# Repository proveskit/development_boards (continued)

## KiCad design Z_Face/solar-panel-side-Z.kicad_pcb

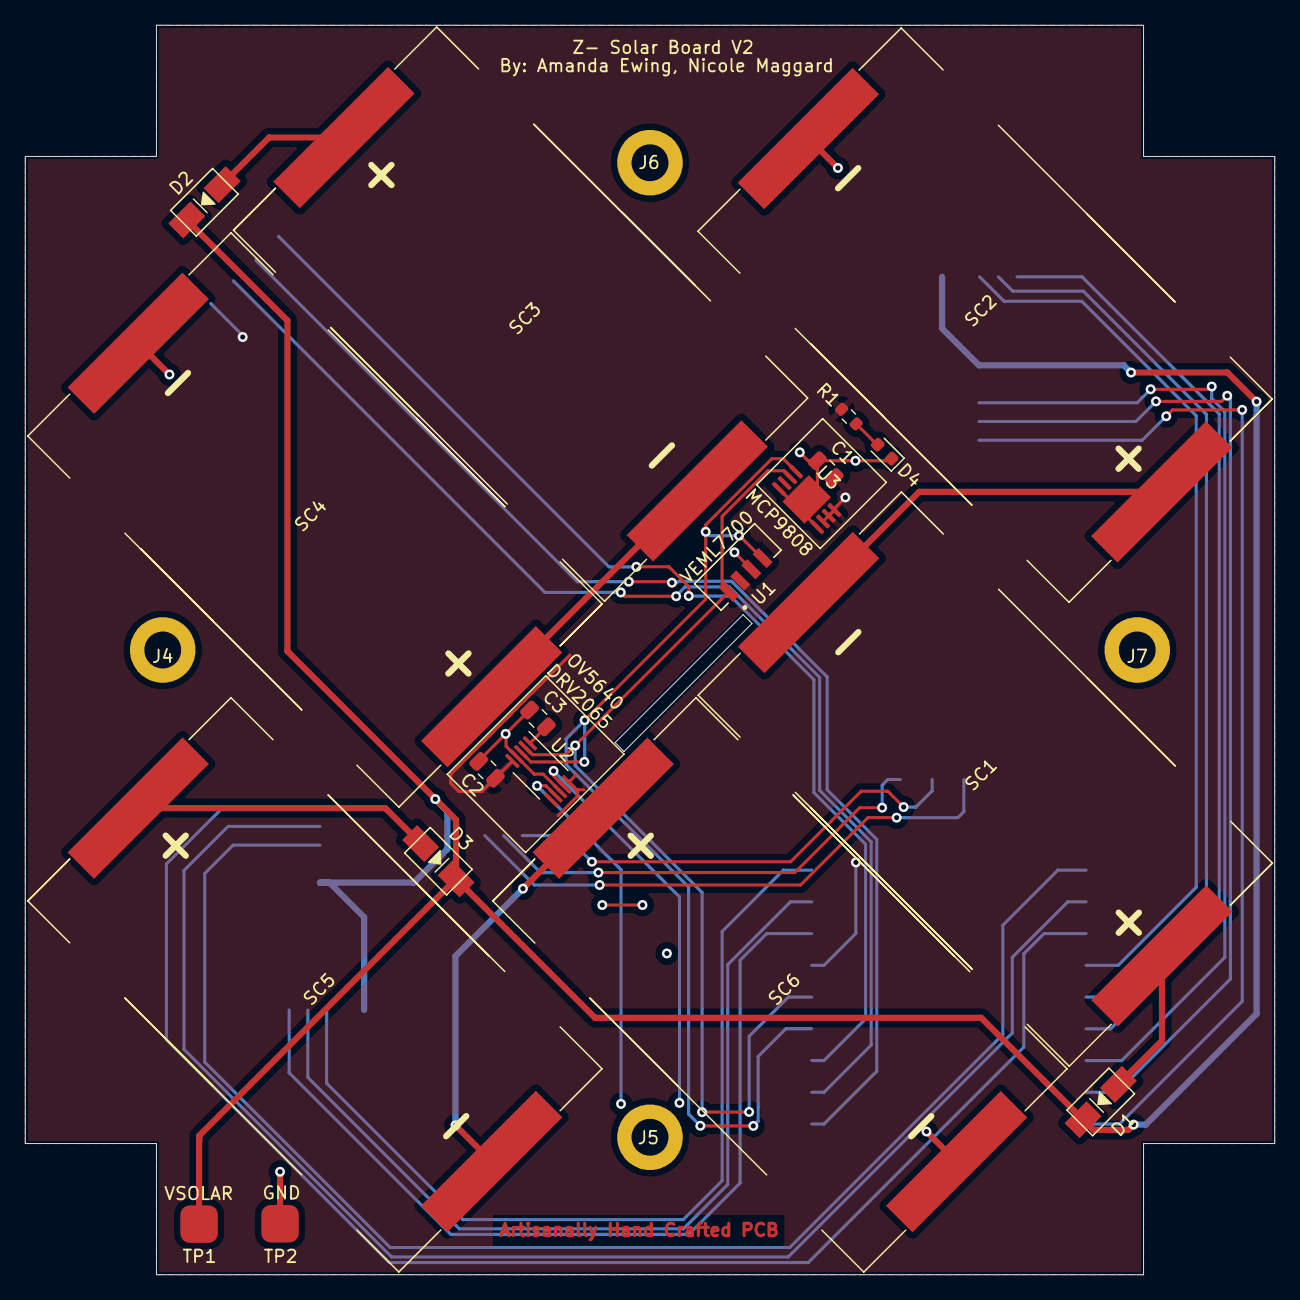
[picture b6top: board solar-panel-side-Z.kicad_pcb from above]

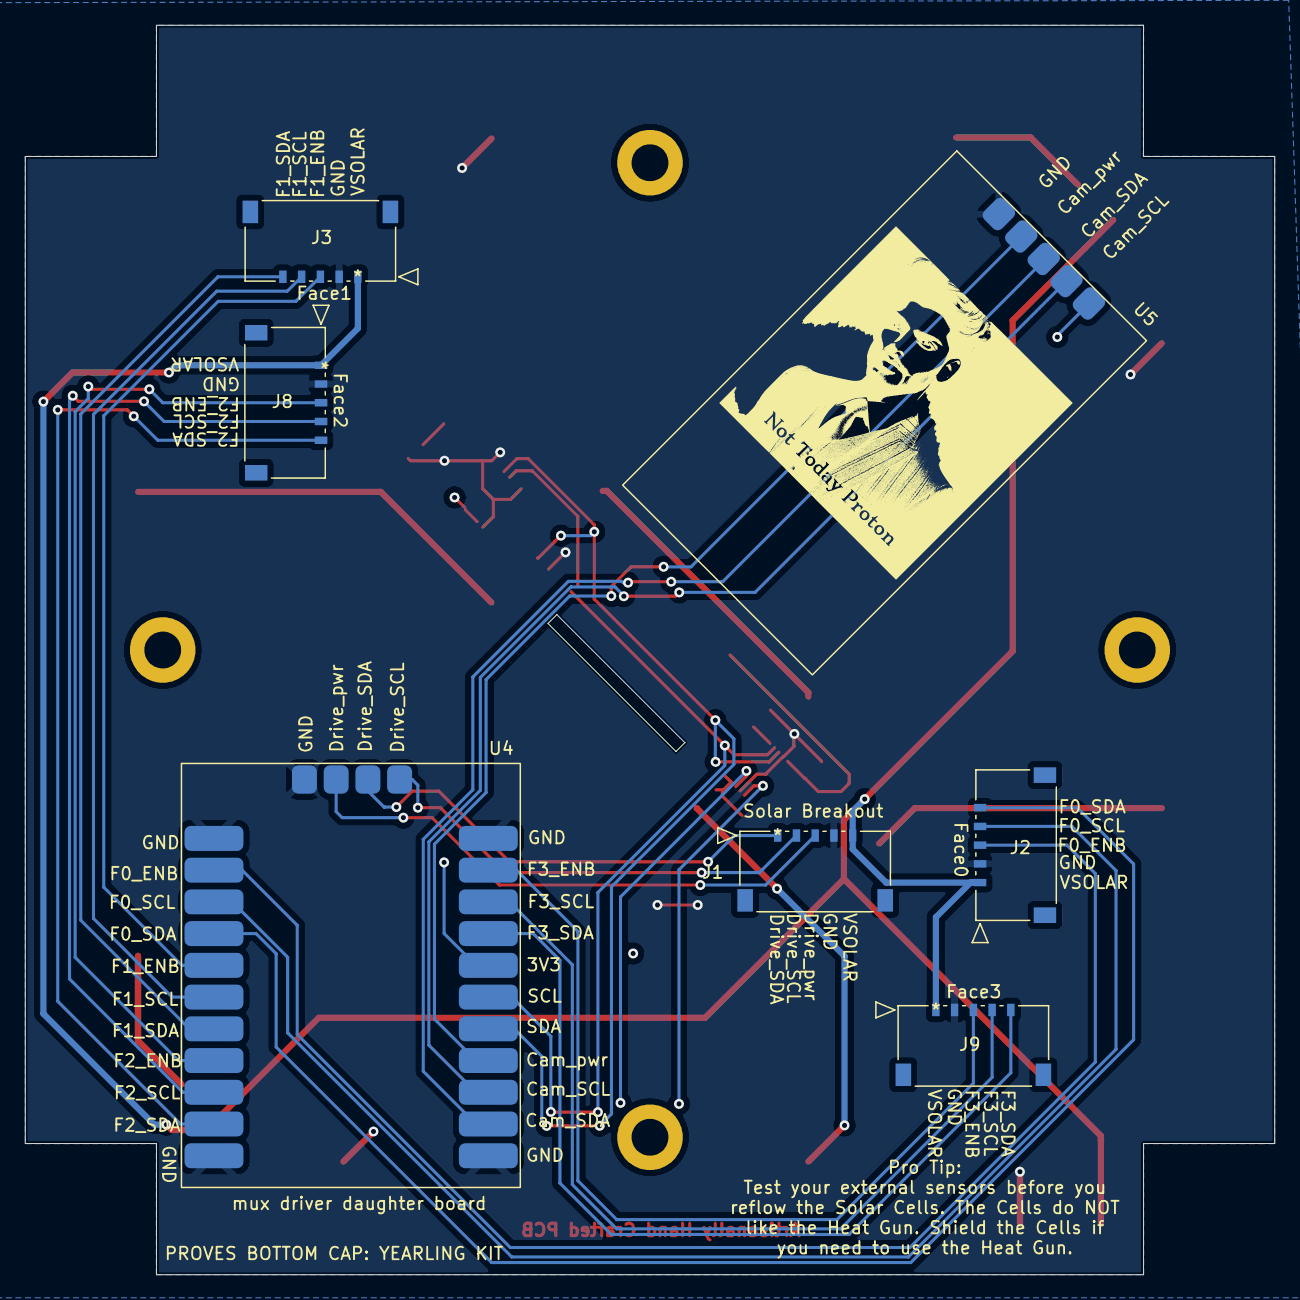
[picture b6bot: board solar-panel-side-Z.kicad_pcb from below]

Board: 4 copper layers, 100.0 x 100.0 mm, 30 parts (7 on the bottom side), 32 nets.

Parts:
C1, C2, C3: 1uF; C_0805_2012Metric
D1, D2, D3: CDBA240LL-HF; DO-214AC
D4: CQY99; LED_0603_1608Metric
J1: CON-5040500591; CON_5040500591
J2: Face0; CON_5040500591
J3: Face1; CON_5040500591
J4, J5, J6, J7: Conn_01x01; MountingHoles
J8: Face2; CON_5040500591
J9: Face3; CON_5040500591
R1: 1k; R_0603_1608Metric
SC1, SC2, SC3, SC4, SC5, SC6: SM101K07TF; KXOB101K08F-TR
TP1, TP2: TestPoint; Test Pad
U1: VEML7700; XDCR_VEML7700-TT
U2: DRV2605LDGS; VSSOP-10_3x3mm_P0.5mm
U3: MCP9808_DFN; MSOP-8-1EP_3x3mm_P0.65mm_EP2.5x3mm_Mask1.73x2.36mm
U4: mux_driver
U5: camera_daughter

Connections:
3v3_break: J1.3, U4.24 (3V3)
+3V3: C1.1, C2.1, R1.1, U1.2 (VDD), U2.5 (EN), U2.10 (VDD), U3.6 (A1), U3.7 (A0), U3.8 (VDD), U4.16 (F4PWR), U5.5 (3V3)
Camera_Pwr: U4.19 (XPWR), U5.2 (ctrl)
Camera_SCL: U4.20 (XSCL), U5.4 (SCL)
Camera_SDA: U4.21 (XSDA), U5.3 (SDA)
F0_ENB: J2.3, U4.2 (F0PWR)
F0_SCL: J2.4, U4.3 (F0SCL)
F0_SDA: J2.5, U4.4 (F0SDA)
F1_ENB: J3.3, U4.5 (F1PWR)
F1_SCL: J3.4, U4.6 (F1SCL)
F1_SDA: J3.5, U4.7 (F1SDA)
F2_ENB: J8.3, U4.8 (F2PWR)
F2_SCL: J8.4, U4.9 (F2SCL)
F2_SDA: J8.5, U4.10 (F2SDA)
F3_ENB: J9.3, U4.13 (F3PWR)
F3_SCL: J9.4, U4.14 (F3SCL)
F3_SDA: J9.5, U4.15 (F3SDA)
GND: C1.2, C2.2, C3.2, D4.1 (K), J1.4, J2.2, J3.2, J8.2, J9.2, SC2.2 (-), SC4.2 (-), SC6.2 (-), TP2.1, U1.3 (GND), U2.4 (IN/TRIG), U2.8 (GND), U3.4 (GND), U3.5 (A2), U3.9 (EP/GND), U4.1 (GND), U4.11 (GND), U4.12 (GND), U4.22 (GND), U4.23 (GND), U5.1 (GND)
unnamed: D1.2 (A), SC1.1 (+)
unnamed: D2.2 (A), SC3.1 (+)
unnamed: D3.2 (A), SC5.1 (+)
unnamed: D4.2 (A), R1.2
unnamed: SC1.2 (-), SC2.1 (+)
unnamed: SC3.2 (-), SC4.1 (+)
unnamed: SC5.2 (-), SC6.1 (+)
unnamed: U2.7 (OUT+), U2.9 (OUT-)
unnamed: C3.1, U2.1 (REG)
SCL: U1.1 (SCL), U2.2 (SCL), U3.2 (SCL), U4.17 (F4SCL)
SCL_Break: J1.2, U4.26 (SCL)
SDA: U1.4 (SDA), U2.3 (SDA), U3.1 (SDA), U4.18 (F4SDA)
SDA_Break: J1.1, U4.25 (SDA)
VSOLAR: D1.1 (K), D2.1 (K), D3.1 (K), J1.5, J2.1, J3.1, J8.1, J9.1, TP1.1

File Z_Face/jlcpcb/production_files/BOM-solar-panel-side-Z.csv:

Comment,Designator,Footprint,LCSC
MCP9808_DFN,U3,MSOP-8-1EP_3x3mm_P0.65mm_EP2.5x3mm_Mask1.73x2.36mm,C129490
VEML7700,U1,XDCR_VEML7700-TT,C1850416
1k,R1,R_0603_1608Metric,C21190
CQY99,D4,LED_0603_1608Metric,C2288
1uF,"C1,C2,C3",C_0805_2012Metric,C28323
CDBA240LL-HF,"D1,D2,D3",DO-214AC,C2886093
DRV2605LDGS,U2,VSSOP-10_3x3mm_P0.5mm,C527464
Conn_01x01,J4,MountingHoles,
Conn_01x01,J5,MountingHoles,
Conn_01x01,J6,MountingHoles,
Conn_01x01,J7,MountingHoles,
TestPoint,TP1,Test Pad,
SM101K07TF,SC5,KXOB101K08F-TR,
TestPoint,TP2,Test Pad,
SM101K07TF,SC3,KXOB101K08F-TR,
SM101K07TF,SC4,KXOB101K08F-TR,
SM101K07TF,SC6,KXOB101K08F-TR,
SM101K07TF,SC1,KXOB101K08F-TR,
CON-5040500591,J1,CON_5040500591,
~,U5,camera_daughter,
Face0,J2,CON_5040500591,
Face1,J3,CON_5040500591,
~,U4,mux_driver,
SM101K07TF,SC2,KXOB101K08F-TR,
Face3,J9,CON_5040500591,
Face2,J8,CON_5040500591,

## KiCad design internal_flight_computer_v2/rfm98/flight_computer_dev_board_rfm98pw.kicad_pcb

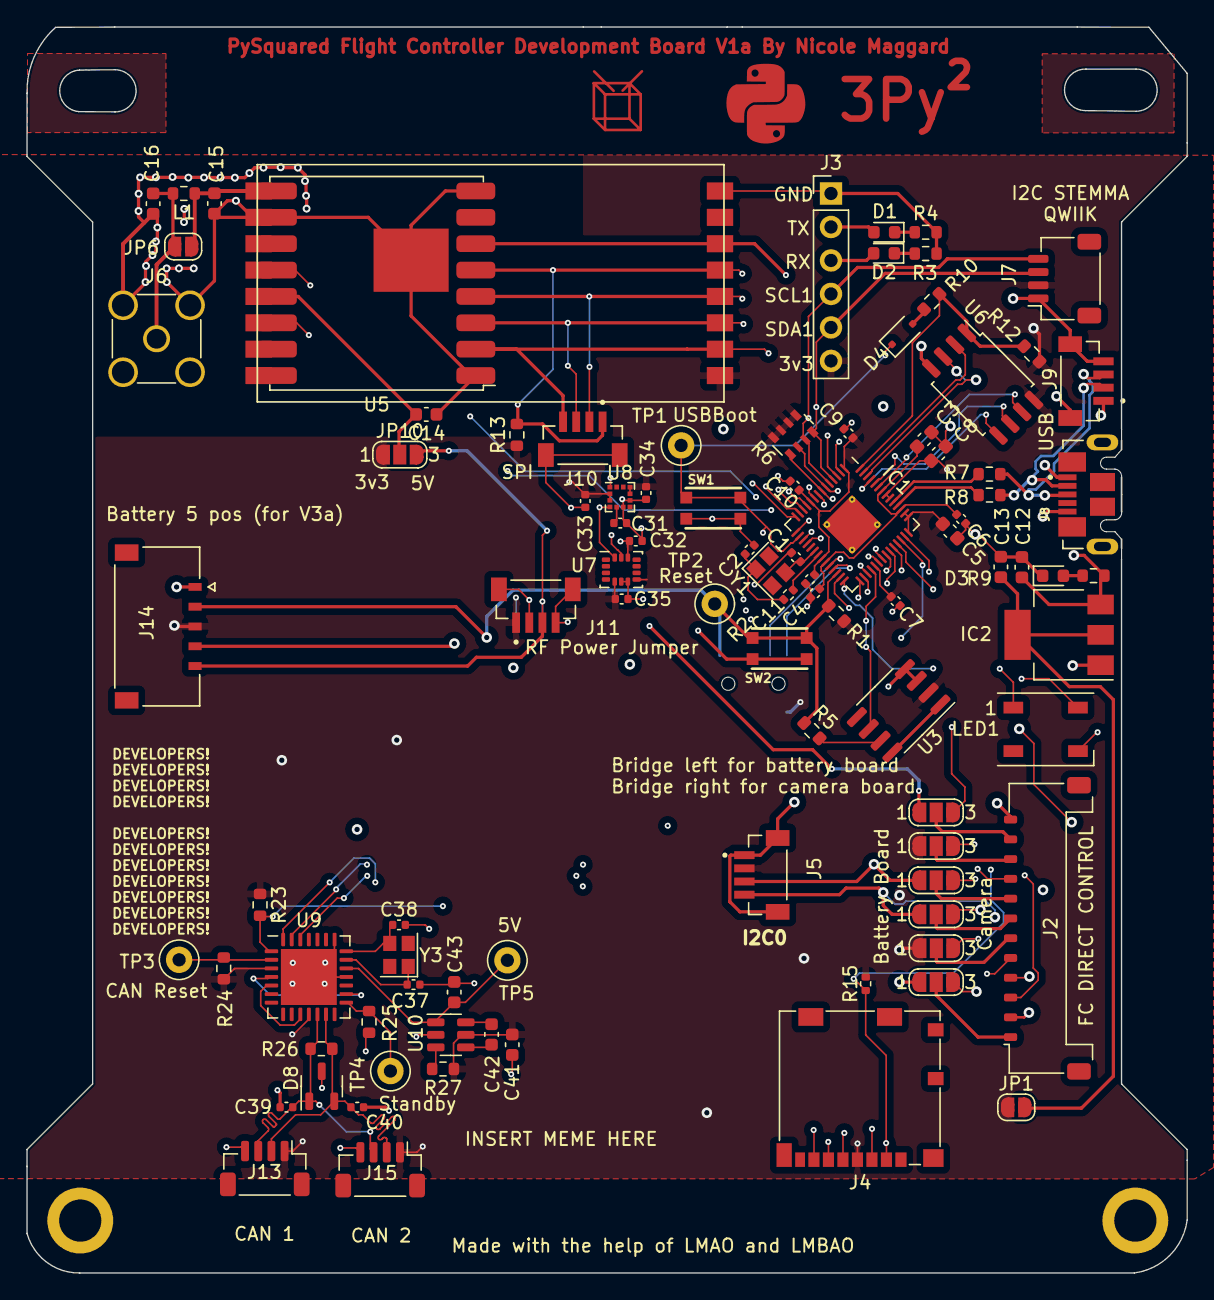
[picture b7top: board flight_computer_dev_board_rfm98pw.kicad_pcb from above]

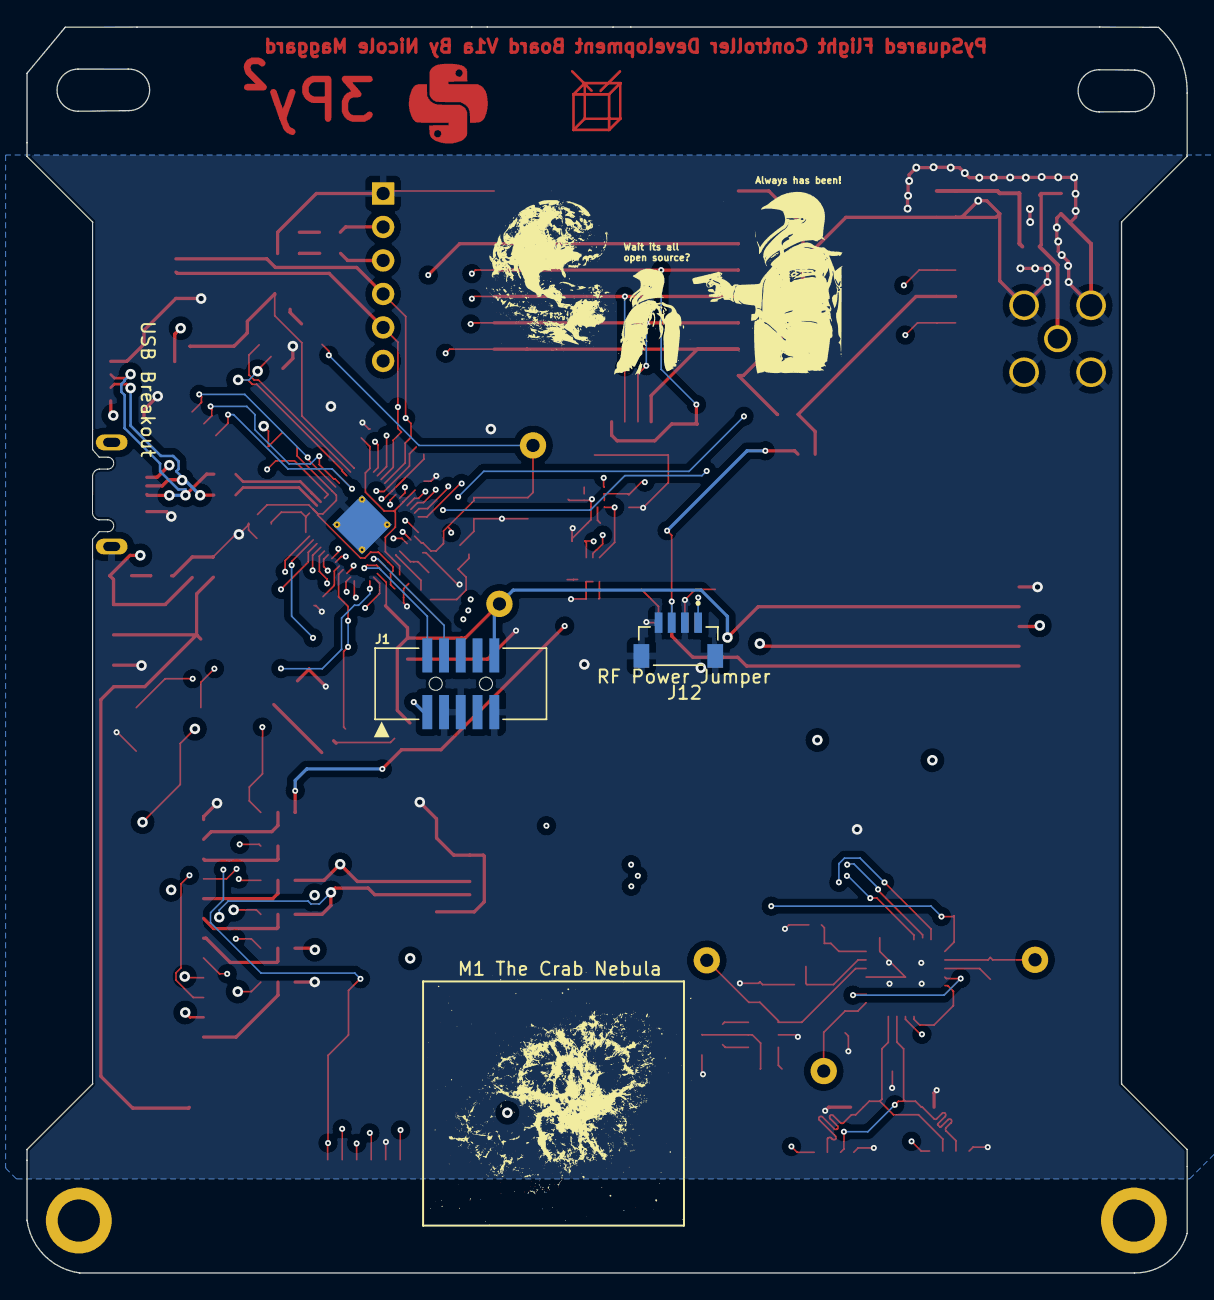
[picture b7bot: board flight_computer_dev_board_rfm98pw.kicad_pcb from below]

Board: 4 copper layers, 88.0 x 94.5 mm, 96 parts (2 on the bottom side), 80 nets.

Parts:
C1, C2: 22pF; C_0402_1005Metric
C3, C6, C8: 1uF; C_0603_1608Metric
C4, C5, C7, C9, C10, C11, C32, C33, C34, C35: 100nf; C_0402_1005Metric
C12, C14: 10uF; C_0603_1608Metric
C13: 22uF; C_0603_1608Metric
C15, C16: DNI; C_0603_1608Metric
C31: 220nf; C_0402_1005Metric
C37, C38: 22pf; C_0402_1005Metric
C39, C40: 47pf; C_0402_1005Metric
C41, C43: 10uf; C_0603_1608Metric
C42: 1uf; C_0603_1608Metric
D1, D2, D3: LED; LED_0603_1608Metric
D4: NSR0320; D_SOD-323F
D8: PESD1CAN; SOT-23-3
IC1: RP2040_QFN56; QFN-56-1EP_7x7mm_P0.4mm_EP3.2x3.2mm_ThermalVias
IC2: AZ1117CH-3.3TRG1; SOT-223
J1: Conn_ARM_JTAG_SWD_10; JTAG_2X05_1.27MM_BOX_NOCREAM
J2: FC to EPS Connector; Molex_Pico-Lock_504050-1291_1x12-1MP_P1.50mm_Horizontal
J3: Life Makes Lemonade; PinHeader_1x06_P2.54mm_Vertical
J4: 104031-0811; microSD_HC_Molex_104031-0811
J5, J9, J10, J11, J12: BM04B-SRSS-TB(LF)(SN); JST_BM04B-SRSS-TB(LF)(SN)
J6: Conn_Coaxial; SMA_Amphenol_901-144_Vertical
J7: Breakout; JST_SH_SM04B-SRSS-TB_1x04-1MP_P1.00mm_Horizontal
J8: USB_B_Micro; MOLEX_105164-0001
J13, J15: Breakout; JST_SH_BM04B-SRSS-TB_1x04-1MP_P1.00mm_Vertical
J14: Battery; MOLEX_5040500591
JP1, JP6: SolderJumper_2_Open; SolderJumper-2_P1.3mm_Open_RoundedPad1.0x1.5mm
JP3, JP4, JP5, JP7, JP8, JP9, JP10: Jumper_3_Open; SolderJumper-3_P1.3mm_Open_RoundedPad1.0x1.5mm_NumberLabels
L1: DNI; R_0603_1608Metric
LED1: WS2812B_SK6812_1515; LED_WS2812B_PLCC4_5.0x5.0mm_P3.2mm
R1, R5, R9, R12, R13, R23, R24, R25, R27: 10k; R_0603_1608Metric
R2: 1k; R_0402_1005Metric
R3, R4, R10: 1k; R_0603_1608Metric
R6: 10k; R_Array_Convex_4x0603
R7, R8: 22; R_0603_1608Metric
R15: 10k; R_0402_1005Metric
R26: 120; R_0603_1608Metric
SW1, SW2: KMR2; BTN_KMR2_4.6X2.8
TP1: USBBOOT; TestPoint_Loop_D1.80mm_Drill1.0mm_Beaded
TP2, TP3: RESET; TestPoint_Loop_D1.80mm_Drill1.0mm_Beaded
TP4: Standby; TestPoint_Loop_D1.80mm_Drill1.0mm_Beaded
TP5: 5V; TestPoint_Loop_D1.80mm_Drill1.0mm_Beaded
U3: MAX706RESA; SO-8_3.9x4.9mm_P1.27mm
U4: RFM98PW
U5: RFM9xBreakout; HOPERF_RFM9XW_SMD
U6: W25Q128JV; SOIC-8_5.275x5.275mm_P1.27mm
U7: LSM6DSOTR; LGA-14_3x2.5mm_P0.5mm_LayoutBorder3x4y
U8: LSM303AGRTR; LGA-12_2x2mm_P0.5mm
U9: MCP25625-E/ML; QFN-28-1EP_6x6mm_P0.65mm_EP4.25x4.25mm
U10: AP3602AKTR-G1; SOT-23-6
Y1: 12MHZ; Crystal_SMD_2520-4Pin_2.5x2.0mm
Y3: 16MHZ 12 pf; Crystal_SMD_2520-4Pin_2.5x2.0mm

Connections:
1.2V: C3.1, C4.2, C5.2, IC1.23 (DVDD), IC1.45 (VREG_VOUT), IC1.50 (DVDD)
3.3V: C6.1, C7.1, C8.1, C9.1, C10.1, C11.1, C32.1, C33.1, C34.1, C35.1, C41.2, IC1.1 (IOVDD), IC1.10 (IOVDD), IC1.22 (IOVDD), IC1.33 (IOVDD), IC1.42 (IOVDD), IC1.43 (ADC_IOVDD), IC1.44 (VREG_IOVDD), IC1.48 (USB_IOVDD), IC1.49 (IOVDD), J1.1 (VTref), J3.6, J4.4 (VDD), J5.2, J7.2, J11.1, J12.1, J13.1, J14.3, J15.1, JP1.1 (A), JP4.1 (A), JP5.1 (A), JP10.1 (A), R1.1, R6.5 (R4.2), R6.6 (R3.2), R6.7 (R2.2), R6.8 (R1.2), R12.1, R13.1, R15.2, R23.1, R24.1, R27.1, U3.2 (VCC), U4.9 (3.3V), U6.8 (VCC), U7.5 (VDDIO), U7.8 (VDD), U7.12 (CS), U8.2 (CS_XL), U8.3 (CS_MAG), U8.9 (VDD), U8.10 (VDD_IO), U9.3 (VDD@1), U9.11 (VIO), U10.5 (VIN)
3v3 Spec: C13.1, IC2.2 (OUTPUT), IC2.4 (VOUT), JP1.2 (B)
+5V: C43.2, TP5.1, U9.19 (VDDA), U10.1 (VOUT)
/D+: IC1.47 (USB_D+), R7.1
/D-: IC1.46 (USB_D-), R8.1
/QSPI_CS: IC1.56 (~QSPI_CS), R10.1, R12.2, U6.1 (SSEL)
/QSPI_DATA[0]: IC1.53 (QSPI_SD0), U6.5 (MOSI)
/QSPI_DATA[1]: IC1.55 (QSPI_SD1), U6.2 (MISO)
/QSPI_DATA[2]: IC1.54 (QSPI_SD2), U6.3 (WP#/IO2)
/QSPI_DATA[3]: IC1.51 (QSPI_SD3), U6.7 (HOLD#/IO3)
/QSPI_SCK: IC1.52 (QSPI_SCLK), U6.6 (SCK)
BURN_RELAY_A / D5: IC1.18 (GPIO15), JP9.3 (B)
CANH: C40.2, D8.2, J13.2, J15.2, R26.2, U9.13 (CANH)
CANL: C39.1, D8.1, J13.3, J15.3, R26.1, U9.12 (CANL)
D0: IC1.41 (GPIO29/AD3), J14.4
D3: D4.1 (K), IC1.16 (GPIO13), J2.5, SW1.A, SW1.A' (P1), TP1.1
D6: IC1.27 (GPIO16), JP8.3 (B)
D7: IC1.28 (GPIO17), J2.9
D8: IC1.29 (GPIO18), JP5.3 (B)
D9: IC1.30 (GPIO19), JP7.3 (B)
ENABLE_BURN / PC: IC1.8 (GPIO6), J2.3
ENAB_RF / D2: IC1.15 (GPIO12), J2.4
FC_RESET: IC1.26 (/RUN), J1.10 (~RESET), J14.2, R1.2, R5.1, SW2.A, SW2.A' (P1), TP2.1
GND: C1.1, C2.1, C3.2, C4.1, C5.1, C6.2, C7.2, C8.2, C9.2, C10.2, C11.2, C12.2, C13.2, C14.1, C15.2, C16.2, C31.2, C32.2, C33.2, C34.2, C35.2, C37.2, C38.2, C39.2, C40.1, C41.1, C43.1, D3.1 (K), D8.3, IC1.57 (GND), IC2.1 (ADJ/GND), J1.3 (GND), J1.5 (GND), J1.9 (GNDDetect), J2.12, J3.1, J4.6 (VSS), J5.1, J5.S1 (SHIELD), J5.S2 (SHIELD), J6.2 (Ext), J7.1, J8.5 (GND), J8.SH1 (Shield), J9.4, J9.S1 (SHIELD), J9.S2 (SHIELD), J10.S1 (SHIELD), J10.S2 (SHIELD), J11.2, J11.4, J11.S1 (SHIELD), J11.S2 (SHIELD), J12.2, J12.4, J12.S1 (SHIELD), J12.S2 (SHIELD), J13.4, J14.1, J15.4, JP3.1 (A), LED1.3 (GND), R3.2, R4.2, R25.1, SW1.B (S), SW1.B' (S1), SW2.B (S), SW2.B' (S1), U3.3 (GND), U3.4 (PFI), U4.2 (GND), U4.16 (GND), U4.17 (GND), U5.1 (GND), U5.8 (GND), U5.10 (GND), U6.4 (VSS), U7.6 (GND), U7.7 (GND), U8.6 (GND), U8.8 (GND), U9.18 (VSS@1), U9.22 (GND), U9.29 (GND@1), U10.2 (GND)
HS: IC1.37 (GPIO25), JP3.3 (B)
I2C_RESET / VS: IC1.9 (GPIO7), J2.2
NEOPIX: IC1.36 (GPIO24), LED1.4 (DI)
Neo_pwr: IC1.39 (GPIO27/AD1), LED1.1 (VDD)
unnamed: C2.2, R2.2, Y1.1
unnamed: D1.1 (K), R4.1
unnamed: D2.1 (K), R3.1
unnamed: D3.2 (A), R9.2
unnamed: D4.2 (A), R10.2
unnamed: C1.2, IC1.20 (XIN), Y1.3 (2)
unnamed: IC1.21 (XOUT), R2.1
unnamed: J2.1, JP3.2 (C)
unnamed: J2.6, JP4.2 (C)
unnamed: J2.7, JP9.2 (C)
unnamed: J2.8, JP8.2 (C)
unnamed: J2.10, JP5.2 (C)
unnamed: J2.11, JP7.2 (C)
unnamed: C16.1, J6.1 (In), JP6.1 (A), L1.2
unnamed: U3.1 (~MR), U3.8 (~WDO)
unnamed: R5.2, U3.7 (~RESET)
unnamed: C31.1, U8.5 (C1)
unnamed: C38.1, U9.21 (OSC1), Y3.3 (2)
unnamed: C37.1, U9.20 (OSC2), Y3.1
unnamed: R24.2, TP3.1, U9.2 (RESET)
unnamed: R25.2, TP4.1, U9.15 (STBY)
unnamed: R27.2, U10.3 (*SHDN)
unnamed: C42.2, U10.6 (C+)
unnamed: C42.1, U10.4 (C-)
RF1_ANT: C15.1, JP6.2 (B), L1.1, U4.1 (ANT), U5.9 (ANT)
RF1_IO0: IC1.35 (GPIO23), U4.6 (GPIO_0), U5.14 (DIO0)
RF1_IO4: IC1.34 (GPIO22), U4.4 (GPIO_4), U5.12 (BUSY)
RF1_RST: IC1.31 (GPIO20), U4.14 (RESET), U5.6 (~RESET)
RF_VCC: C14.2, JP10.2 (C), U4.5 (VCC), U5.13 (3V3)
RX: D2.2 (A), IC1.3 (GPIO1), J3.3
RXCAN: U9.5 (RXCAN), U9.10 (RXD)
SCL0: IC1.7 (GPIO5), J5.4, JP9.1 (A), R6.1 (R1.1)
SCL1: IC1.5 (GPIO3), J3.4, J7.4, R6.3 (R3.1), U7.13 (SCL), U8.1 (SCL/SPC)
SDA0: IC1.6 (GPIO4), J5.3, JP8.1 (A), R6.2 (R2.1)
SDA1: IC1.4 (GPIO2), J3.5, J7.3, R6.4 (R4.1), U7.14 (SDA), U8.4 (SDA/SDI/SDO)
SPI0_CS0: IC1.12 (GPIO9), J10.1, R13.2, U4.13 (NSS), U5.5 (CS)
SPI0_CS1: IC1.38 (GPIO26/AD0), J4.2 (CD/DAT3), R15.1
SPI0_CS2: IC1.40 (GPIO28/AD2), R23.2, U9.1 (CS)
SPI0_MISO: IC1.11 (GPIO8), J4.7 (DAT0), J10.4, U4.10 (MISO), U5.2 (MISO), U9.28 (SO)
SPI0_MOSI: IC1.14 (GPIO11), J4.3 (CMD), J10.3, U4.11 (MOSI), U5.3 (MOSI), U9.27 (SI)
SPI0_SCK: IC1.13 (GPIO10), J4.5 (CLK), J10.2, U4.12 (SCK), U5.4 (SCK), U9.26 (SCK)
SWCLK: IC1.24 (SWCLK), J1.4 (SWDCLK/TCK)
SWDIO: IC1.25 (SWDIO), J1.2 (SWDIO/TMS)
TX: D1.2 (A), IC1.2 (GPIO0), J3.2
TXCAN: U9.4 (TXCAN), U9.16 (TXD)
USB_D+: J8.3 (D+), J9.3, R7.2
USB_D-: J8.2 (D-), J9.2, R8.2
VBUS: C12.1, IC2.3 (INPUT), J8.1 (VBUS), J9.1, R9.1
VBUS_RESET / D4: IC1.17 (GPIO14), JP4.3 (B)
VCC_RF1: J11.3, J12.3, J14.5, JP7.1 (A), JP10.3 (B)
WDT_WDI: IC1.32 (GPIO21), U3.6 (~WDI)

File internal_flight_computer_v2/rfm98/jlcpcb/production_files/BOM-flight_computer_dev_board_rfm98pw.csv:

Comment,Designator,Footprint,LCSC
10k,R6,R_Array_Convex_4x0603,C111802
1k,R2,R_0402_1005Metric,C11702
LED,"D1,D3",LED_0603_1608Metric,C12065
LSM303AGRTR,U8,LGA-12_2x2mm_P0.5mm,C126671
100nf,"C10,C11,C32,C33,C34,C35,C4,C5,C7,C9",C_0402_1005Metric,C1525
22pF,"C1,C2,C37,C38",C_0402_1005Metric,C1555
47pf,"C39,C40",C_0402_1005Metric,C1567
PESD1CAN,D8,SOT-23-3,C15771
1uF,"C3,C42,C6,C8",C_0603_1608Metric,C15849
BM04B-SRSS-TB(LF)(SN),"J10,J11,J12,J5,J9",JST_BM04B-SRSS-TB(LF)(SN),C160390
Breakout,"J13,J15,J7",JST_SH_SM04B-SRSS-TB_1x04-1MP_P1.00mm_Horizontal,C160404
220nf,C31,C_0402_1005Metric,C16772
MCP25625-E/ML,U9,QFN-28-1EP_6x6mm_P0.65mm_EP4.25x4.25mm,C191253
10uF,"C12,C14,C41,C43",C_0603_1608Metric,C19702
RP2040_QFN56,IC1,QFN-56-1EP_7x7mm_P0.4mm_EP3.2x3.2mm_ThermalVias,C2040
1k,"R10,R3,R4",R_0603_1608Metric,C21190
120,R26,R_0603_1608Metric,C22787
LED,D2,LED_0603_1608Metric,C2286
22,"R7,R8",R_0603_1608Metric,C23345
USB_B_Micro,J8,MOLEX_105164-0001,C234179
12MHZ,Y1,Crystal_SMD_2520-4Pin_2.5x2.0mm,C252259
10k,R15,R_0402_1005Metric,C25744
10k,"R1,R12,R13,R23,R24,R25,R27,R5,R9",R_0603_1608Metric,C25804
LSM6DSOTR,U7,LGA-14_3x2.5mm_P0.5mm_LayoutBorder3x4y,C2655100
MAX706RESA,U3,SO-8_3.9x4.9mm_P1.27mm,C28380
16MHZ 12 pf,Y3,Crystal_SMD_2520-4Pin_2.5x2.0mm,C284158
WS2812B_SK6812_1515,LED1,LED_WS2812B_PLCC4_5.0x5.0mm_P3.2mm,C2843785
AP3602AKTR-G1,U10,SOT-23-6,C460358
NSR0320,D4,D_SOD-323F,C48192
104031-0811,J4,microSD_HC_Molex_104031-0811,C585350
22uF,C13,C_0603_1608Metric,C59461
KMR2,"SW1,SW2",BTN_KMR2_4.6X2.8,C72443
AZ1117CH-3.3TRG1,IC2,SOT-223,C92102
W25Q128JV,U6,SOIC-8_5.275x5.275mm_P1.27mm,C97521
Conn_Coaxial,J6,SMA_Amphenol_901-144_Vertical,
DNI,C16,C_0603_1608Metric,
DNI,L1,R_0603_1608Metric,
SolderJumper_2_Open,JP1,SolderJumper-2_P1.3mm_Open_RoundedPad1.0x1.5mm,
DNI,C15,C_0603_1608Metric,
RFM98PW,U4,RFM98PW,
RESET,TP2,TestPoint_Loop_D1.80mm_Drill1.0mm_Beaded,
SolderJumper_2_Open,JP6,SolderJumper-2_P1.3mm_Open_RoundedPad1.0x1.5mm,
Jumper_3_Open,JP5,SolderJumper-3_P1.3mm_Open_RoundedPad1.0x1.5mm_NumberLabels,
RFM9xBreakout,U5,HOPERF_RFM9XW_SMD,
Jumper_3_Open,JP4,SolderJumper-3_P1.3mm_Open_RoundedPad1.0x1.5mm_NumberLabels,
FC to EPS Connector,J2,Molex_Pico-Lock_504050-1291_1x12-1MP_P1.50mm_Horizontal,
USBBOOT,TP1,TestPoint_Loop_D1.80mm_Drill1.0mm_Beaded,
Jumper_3_Open,JP3,SolderJumper-3_P1.3mm_Open_RoundedPad1.0x1.5mm_NumberLabels,
Life Makes Lemonade,J3,PinHeader_1x06_P2.54mm_Vertical,
Conn_ARM_JTAG_SWD_10,J1,JTAG_2X05_1.27MM_BOX_NOCREAM,
Jumper_3_Open,JP8,SolderJumper-3_P1.3mm_Open_RoundedPad1.0x1.5mm_NumberLabels,
Standby,TP4,TestPoint_Loop_D1.80mm_Drill1.0mm_Beaded,
RESET,TP3,TestPoint_Loop_D1.80mm_Drill1.0mm_Beaded,
Jumper_3_Open,JP7,SolderJumper-3_P1.3mm_Open_RoundedPad1.0x1.5mm_NumberLabels,
5V,TP5,TestPoint_Loop_D1.80mm_Drill1.0mm_Beaded,
Jumper_3_Open,JP9,SolderJumper-3_P1.3mm_Open_RoundedPad1.0x1.5mm_NumberLabels,
Battery,J14,MOLEX_5040500591,
Jumper_3_Open,JP10,SolderJumper-3_P1.3mm_Open_RoundedPad1.0x1.5mm_NumberLabels,

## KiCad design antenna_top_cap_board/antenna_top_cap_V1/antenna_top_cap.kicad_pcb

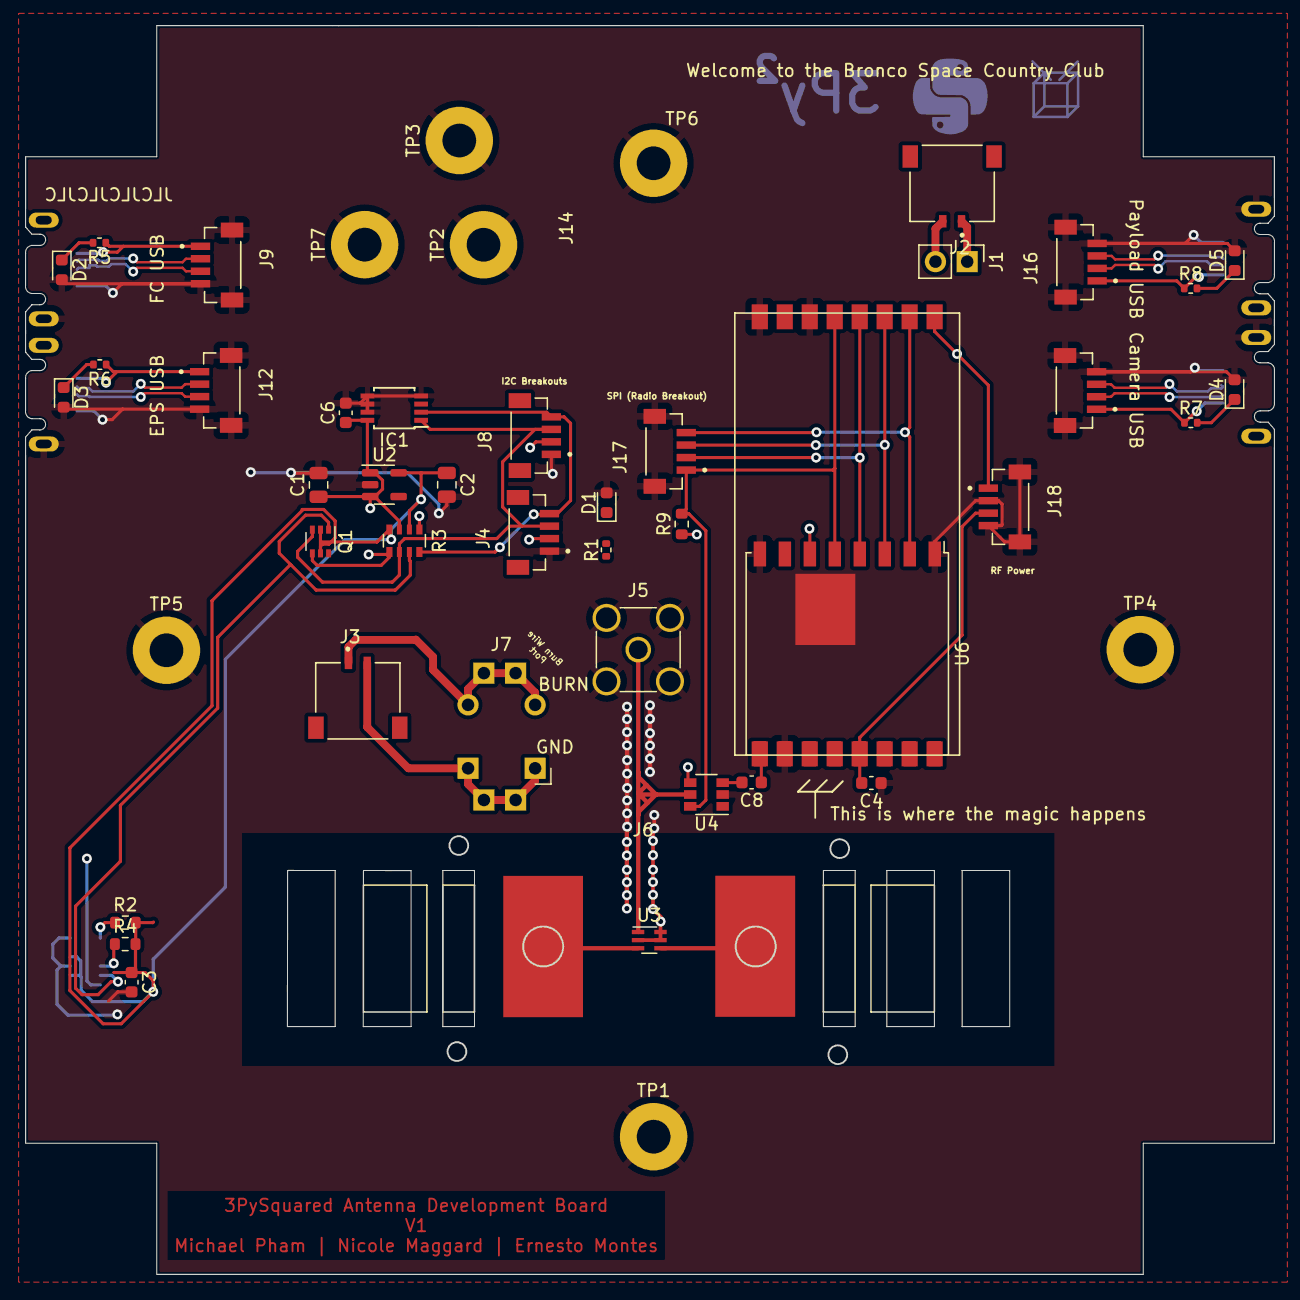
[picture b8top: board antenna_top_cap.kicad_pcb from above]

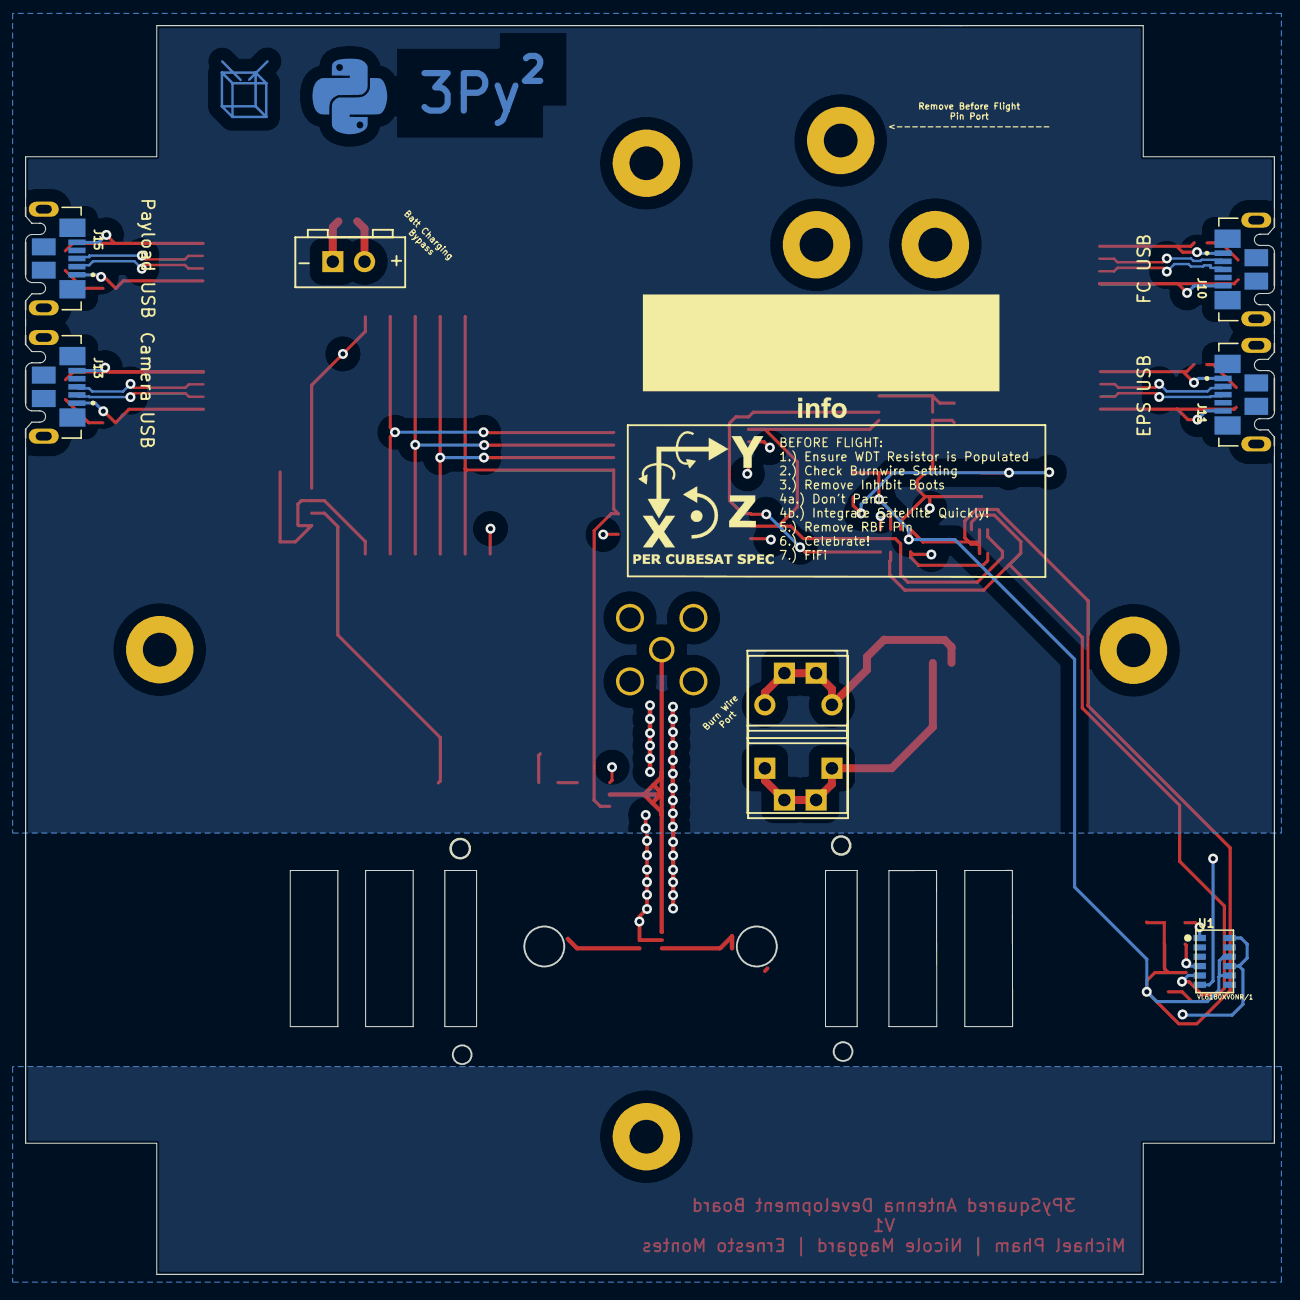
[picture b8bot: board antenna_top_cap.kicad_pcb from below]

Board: 4 copper layers, 100.0 x 100.0 mm, 53 parts (5 on the bottom side), 42 nets.

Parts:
C1, C2: 10uF; C_0805_2012Metric
C3: 0.1uF; C_0603_1608Metric
C4: 10uF; C_0603_1608Metric
C6: 100nf; C_0603_1608Metric
C8: 100pf; C_0603_1608Metric
D1, D2, D3, D4, D5: Blue; LED_0603_1608Metric
IC1: PCT2075DP,118; TSSOP-8_3x3mm_P0.65mm
J1: Battery Charge Bypass; PinHeader_1x02_P2.54mm_Vertical
J2: Battery Charge Bypass; MOLEX_504050-0291
J3: Burn_Wire; MOLEX_504050-0291
J4, J8, J9, J12, J14, J16, J17, J18: BM04B-SRSS-TB(LF)(SN); JST_BM04B-SRSS-TB(LF)(SN)
J5: Conn_Coaxial; SMA_Amphenol_901-144_Vertical
J6: Tape_Measure_Antenna
J7: Burn_Wire
J10, J11, J13, J15: USB_B_Micro; MOLEX_105164-0001(round)
Q1: BSS138; SOT-363_SC-70-6
R1, R5, R6, R7, R8: 1K; R_0402_1005Metric
R2, R4: 10K; R_0603_1608Metric
R3: 10K; R_Array_Convex_4x0603
R9: 10k; R_0603_1608Metric
TP1, TP2, TP3, TP4, TP5, TP6, TP7: TestPoint; MountingHole_2.7mm_M2.5_Pad
U1: VL6180XV0NR/1; VL6180
U2: LP5907-2.8V; SOT-23-5
U3: 0433BM15A0001; Balun_Johanson_0896BM15A0001
U4: AS193-73LF; SuperSOT-6
U5: RFM98PW
U6: RFM9xBreakout; HOPERF_RFM95W_SMD

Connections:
2.8V: C2.1, C3.1, Q1.2 (G), Q1.5 (G), R2.2, R3.2 (1), R3.4 (1), R4.2, U1.8 (AVDD_VCSEL), U1.10 (AVDD), U2.5 (OUT)
3.3V: C1.1, C6.1, IC1.8 (VCC), J4.2, J8.2, J18.1, R1.1, R3.1, R3.3 (1), R9.1, U2.1 (IN), U2.3 (EN), U4.4 (V2), U5.9 (3.3V), U6.6 (~RESET)
/0d+: J11.3 (D+), J12.3
/0d-: J11.2 (D-), J12.2
/1d+: J9.3, J10.3 (D+)
/1d-: J9.2, J10.2 (D-)
/2d+: J13.3 (D+), J14.3
/2d-: J13.2 (D-), J14.2
/3d+: J15.3 (D+), J16.3
/3d-: J15.2 (D-), J16.2
/BATT_NEG: J1.1, J2.1
/BATT_POS: J1.2, J2.2
/GPIO: R2.1, U1.1 (GPIO1)
/SCL_3V: Q1.1 (S), R3.7 (2), U1.5 (SCL)
/SDA_3V: Q1.4 (S), R3.5 (2), U1.6 (SDA)
/XSHUT_2.8V: R4.1, U1.4 (GPIO0)
Balun: J5.1 (In), U3.1, U4.5 (output)
GND: C1.2, C2.2, C3.2, C4.1, C6.2, D1.2 (C), D2.2 (C), D3.2 (C), D4.2 (C), D5.2 (C), IC1.4 (GND), IC1.5 (A2), IC1.6 (A1), IC1.7 (A0), J4.1, J5.2 (Ext), J8.1, J9.4, J9.S1 (SHIELD), J9.S2 (SHIELD), J10.5 (GND), J10.SH1 (Shield), J11.5 (GND), J11.SH1 (Shield), J12.4, J12.S1 (SHIELD), J12.S2 (SHIELD), J13.5 (GND), J13.SH1 (Shield), J14.4, J14.S1 (SHIELD), J14.S2 (SHIELD), J15.5 (GND), J15.SH1 (Shield), J16.4, J16.S1 (SHIELD), J16.S2 (SHIELD), J17.S1 (SHIELD), J17.S2 (SHIELD), J18.2, J18.4, J18.S1 (SHIELD), J18.S2 (SHIELD), TP1.1, TP2.1, TP3.1, TP4.1, TP5.1, TP6.1, TP7.1, U1.9 (AVSS_VCSEL), U1.12 (AVSS), U2.2 (GND), U3.2 (GND), U3.5 (GND), U3.6 (GND), U4.2 (GND), U5.2 (GND), U5.14 (RESET), U5.16 (GND), U5.17 (GND), U6.1 (GND), U6.8 (GND), U6.10 (GND)
unnamed: D1.1 (A), R1.2
unnamed: D2.1 (A), R5.2
unnamed: D3.1 (A), R6.2
unnamed: D4.1 (A), R7.2
unnamed: D5.1 (A), R8.2
unnamed: J3.1, J7.1 (Power)
unnamed: J3.2, J7.2 (GND)
unnamed: J4.S1 (SHIELD), J4.S2 (SHIELD)
unnamed: J6.1 (tape), U3.3
unnamed: J6.2 (tape), U3.4
unnamed: J8.S1 (SHIELD), J8.S2 (SHIELD)
unnamed: J9.1, J10.1 (VBUS), R5.1
unnamed: J11.1 (VBUS), J12.1, R6.1
unnamed: J13.1 (VBUS), J14.1, R7.1
unnamed: J15.1 (VBUS), J16.1, R8.1
unnamed: C8.2, U4.3 (input2)
OUT2: C8.1, U5.1 (ANT), U6.9 (ANT)
RF_VCC: C4.2, J18.3, U5.5 (VCC), U6.13 (3V3)
SCL1: IC1.2 (SCL), J4.4, J8.4, Q1.6 (D), R3.8 (2)
SDA1: IC1.1 (SDA), J4.3, J8.3, Q1.3 (D), R3.6 (2)
SPI0_CS0: J17.1, R9.2, U4.6 (V1), U5.13 (NSS), U6.5 (CS)
SPI0_MISO: J17.4, U5.10 (MISO), U6.2 (MISO)
SPI0_MOSI: J17.3, U5.11 (MOSI), U6.3 (MOSI)
SPI0_SCK: J17.2, U5.12 (SCK), U6.4 (SCK)

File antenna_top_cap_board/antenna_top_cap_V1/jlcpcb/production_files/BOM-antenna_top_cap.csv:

Comment,Designator,Footprint,LCSC
1K,"R1,R5,R6,R7,R8",R_0402_1005Metric,C11702
0.1uF,"C3,C6",C_0603_1608Metric,C14663
BSS138,Q1,SOT-363_SC-70-6,C154900
BM04B-SRSS-TB(LF)(SN),"J12,J14,J16,J9",JST_BM04B-SRSS-TB(LF)(SN),C160390
Breakout,"J4,J8",JST_SH_SM04B-SRSS-TB_1x04-1MP_P1.00mm_Horizontal,C160404
LP5907-2.8V,U2,SOT-23-5,C186700
"PCT2075DP,118",IC1,TSSOP-8_3x3mm_P0.65mm,C192518
USB_B_Micro,"J10,J11,J13,J15",MOLEX_105164-0001,C234179
10K,"R2,R4",R_0603_1608Metric,C25804
VL6180XV0NR/1,U1,VL6180,C2688732
10K,R3,R_Array_Convex_4x0603,C29718
10uF,"C1,C2",C_0805_2012Metric,C440198
Blue,"D1,D2,D3,D4,D5",LED_0603_1608Metric,C72041
Battery Charge Bypass,J1,PinHeader_1x02_P2.54mm_Vertical,
~,J6,Tape_Measure_Antenna,
Battery Charge Bypass,J2,MOLEX_504050-0291,
0433BM15A0001,U3,Balun_Johanson_0896BM15A0001,
~,J7,Burn_Wire,
Conn_Coaxial,J5,SMA_Amphenol_901-144_Vertical,
Burn_Wire,J3,MOLEX_504050-0291,
TestPoint,TP1,MountingHole_2.7mm_M2.5_Pad,
TestPoint,TP3,MountingHole_2.7mm_M2.5_Pad,
TestPoint,TP7,MountingHole_2.7mm_M2.5_Pad,
TestPoint,TP2,MountingHole_2.7mm_M2.5_Pad,
TestPoint,TP5,MountingHole_2.7mm_M2.5_Pad,
TestPoint,TP6,MountingHole_2.7mm_M2.5_Pad,
TestPoint,TP4,MountingHole_2.7mm_M2.5_Pad,

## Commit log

2023-07-16 Flight Controller Development Board V1
    This board was designed with the intent of fitting within the cubesat structure, and being used outside of the structure for software development. A companion board will be developed to act as a radi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
2023-07-17 Flight Computer dev board minor update
2023-07-22 Antenna_top_cap V1
    A development board for the top cap which would connect to the internal FC Development board
2023-08-01 Antenna Top Cap for Development Board
2023-08-01 antenna update
2023-08-01 dev boards
2023-08-01 sx1276 update
2023-08-02 rfm98pw dev board V1 update
2024-01-21 Pushing a set of new dev boards
    - New Antenna Top Cap
    - Battery Board V3 and V3a
    - New Internal FC Boards
    - New Solar Panel with Cutout
2024-01-21 Updated .gitignore
2024-01-22 Huge Restructure of Dev Boards
2024-01-25 Nuking Redundant Files
2024-03-26 Big Update of In Dev Boards
    Mid Term update for all the boards being developed for use by the Irvington Team on Pleiades - Orpheus
2024-03-26 Moved out Dev Software
2024-05-23 Before Mirror
2024-05-23 finished?
    everything is connected, but theres a few errors - idk how significant those are
2024-05-24 might be too big
    added meme to the back - board might be too long
2024-05-24 save before leaving
2024-05-26 small fixes
2024-05-26 initial schematic push of the flat sat
2024-05-27 schematic done?
2024-05-28 layout on flat-sat board nearly done
2024-05-28 What Does This Do?
2024-05-28 added extra pin to z face
    moved it slightly closer also
2024-05-28 Cleaned up some schematics
2024-05-28 Fake Commit
2024-05-29 Updated all the Diodes!
2024-05-29 Updated Camera Board V2 with Production Files
2024-05-29 Consolidating files
2024-05-29 Fixed Antenna Board
2024-05-29 Bruh
2024-05-29 Squashed commit of the following:
    commit 00eb5deb6a6b98af8bd949735851563e80a95d8e
    Author: Michael Pham <61564344+Mikefly123@users.noreply.github.com>
    Date: Tue May 28 21:23:36 2024 -0700
    Fixed Antenna Board
    commit 19aa127bde26713fc6595ccafa6bbc5502f9de77
    Author: Michael Pham <61564344+Mikefly123@users.noreply.github.com>
2024-05-29 Squashed commit of the following:
    commit e254adcde77272bf9c297392939bbb8f65e8d1c6
    Author: Michael Pham <61564344+Mikefly123@users.noreply.github.com>
    Date: Tue May 28 21:23:36 2024 -0700
    Fixed Antenna Board
    commit 045481aa1d64479ef8ca8c2eedf132e30a3c2c12
    Author: Michael Pham <61564344+Mikefly123@users.noreply.github.com>
2024-05-29 Updated GitIgnore
2024-05-30 Updated Production Files
2024-06-01 Fixed References From 3.3V to be all 3V3
2024-06-13 Updated Schematic to Match FlatSat Dev
2024-06-17 Restructuring the Repo
    Moved a bunch of things to an Archive folder. Those boards will now be developed in their mainline repositories.
2024-06-19 initial commit
    sx1276 dev
2024-06-24 Moved FC SX1276 Dev Board to Top Level
2024-06-30 Initial Schematic push
2024-07-17 test
2024-07-17 test 2
2024-07-17 Updated Schematic
2024-07-17 Updated schematic with components
    Added PA and LNA
2024-07-18 Started Rough Layout
2024-07-18 Updated Schematic and continued layout
2024-07-19 Made adjustments to layout
2024-07-23 Added routing to pcb
2024-07-24 fixed routing and attempted via fencing
2024-07-30 assigned parts
2024-09-19 Created Camera Baord V2a
    Corrected placement of the power control PMOS
2025-07-17 Created Sensor Simulator Project
2025-08-26 initial commit for the hat board
2025-08-27 placement with new temp sensor
2025-08-27 finished connections one board, review before copy and clean?
2025-08-28 no design errors faceboard
2025-08-29 excluded the pad errors
2025-08-29 schematic corrections
2025-08-29 after feedback
2025-09-08 changed so only one set of sensors (save money)
2025-09-08 changed so only one set of sensors and each has own bus
2025-09-09 fixed the electrical rules checking
2025-09-12 added modifications for 2 cables
2025-09-16 placement for face baord attachment
2025-09-16 mirror flipped placement
2025-09-16 finihsed connection, need to reroute certain traces ++ double check orientation of connectors
2025-09-17 corrected PCB design
2025-09-17 from mirror board in schem to bwllo bowrd
2025-10-01 diode added
2025-10-02 connect
2025-10-06 no electrical errors added cake:
2025-10-06 added seomc jlcpcb fiels
2025-10-06 added labels
2025-10-06 new resiotr
2025-10-07 Changed Footprint of 56R
2025-10-07 updated database
2025-10-07 new everything should be here
